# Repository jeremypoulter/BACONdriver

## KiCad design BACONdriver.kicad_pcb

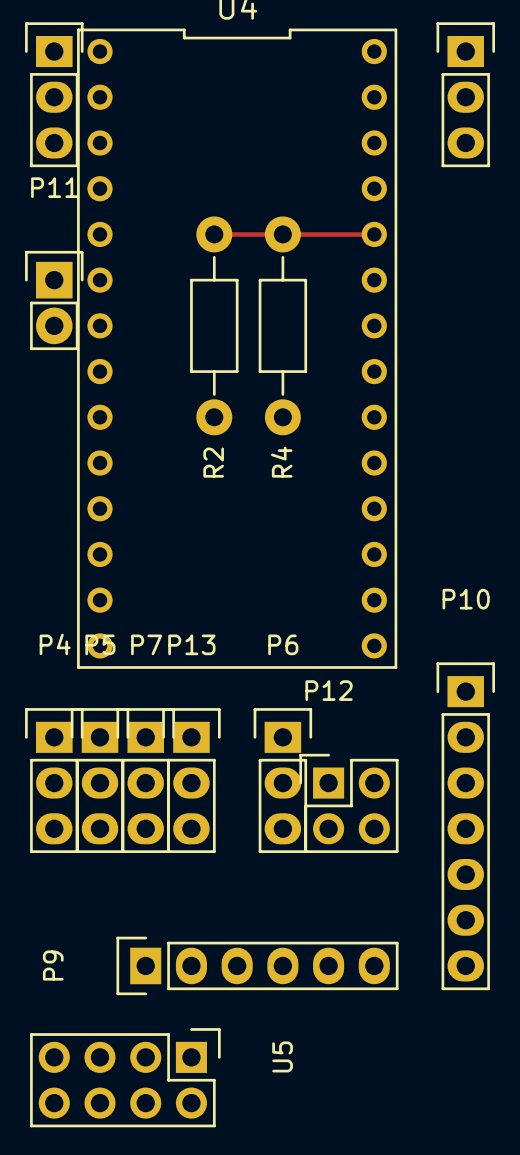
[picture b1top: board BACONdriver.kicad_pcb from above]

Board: 2 copper layers, 15 parts (0 on the bottom side), 27 nets.

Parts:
P1: Batt_Mon; Pin_Header_Straight_1x03
P4: Stearing; Pin_Header_Straight_1x03
P5: D8; Pin_Header_Straight_1x03
P6: V_Sel; Pin_Header_Straight_1x03
P7: A4; Pin_Header_Straight_1x03
P8: Batt_Current; Pin_Header_Straight_1x03
P9: FTDI; Pin_Header_Straight_1x06
P10: Motor_Ctrl; Pin_Header_Straight_1x07
P11: Batt; Pin_Header_Straight_1x02
P12: Cross; Pin_Header_Straight_2x02
P13: A5; Pin_Header_Straight_1x03
R2, R4: 10K; Resistor_Horizontal_RM10mm
U4: Metro_Mini; MetroMini
U5: nRF24L01+; Pin_Header_Straight_2x04

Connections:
+3V3: P6.1, U4.24, U5.2
+5V: P4.2, P5.2, P6.3, P7.2, P8.3, P10.7, P13.2, U4.22
+BATT: P11.2, U4.16
/Control_Board/A0: P1.2, U4.12
/Control_Board/A1: R2.1, R4.2, U4.10
/Control_Board/A4: P7.3, U4.4
/Control_Board/A5: P13.3, U4.2
/Control_Board/CS_VAL: P8.2, U4.8
/Control_Board/Cell2: P1.3, R2.2
/Control_Board/D8: P5.3, U4.17
/Control_Board/MISO: U4.25, U5.7
/Control_Board/MOSI: U4.23, U5.6
/Control_Board/NRF_CS: U4.21, U5.4
/Control_Board/NRF_ENABLE: U4.19, U5.3
/Control_Board/NRF_IRQ: U4.5, U5.8
/Control_Board/RXD: P12.1, U4.1
/Control_Board/SCK: U4.27, U5.5
/Control_Board/STEAR: P4.3, U4.7
/Control_Board/TXD: P12.4, U4.3
/Control_Board/VS_EN: P10.5, U4.15
/Control_Board/VS_INA: P10.2, U4.11
/Control_Board/VS_INB: P10.3, U4.9
/Control_Board/VS_PWM: P10.1, U4.13
GND: P1.1, P4.1, P5.1, P7.1, P8.1, P9.1, P10.6, P11.1, P13.1, R4.1, U4.18, U4.20, U5.1
unnamed: P6.2, P9.3
unnamed: P9.5, P12.2
unnamed: P9.4, P12.3

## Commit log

2015-10-15 Initial version of the electronics for BACON.
2016-02-04 KiCAD cache library file
2016-02-04 Initial version of the firmware for the BACONdriver
2016-02-10 Changes to match prototype, adding an nRF24L01 for receiving control commands from the original transmitter and an FTDI style header for future expansion.
2016-02-11 Various updates; - Break out spare pins - Use the motor driver CS for motor current (Current Sense not Chip Select) - Allow the FTDI Vcc to be switched between 3.3v and 5v
2016-02-11 Moved the components that need laying out to a sub-sheet so the net list can be generated for just those components, while also maintaining the high level wiring
2016-02-11 Initial layout of the control board to get positioning for making up on some prototyping board.
2016-02-16 Modified to use a simple voltage divider for battery voltage measurement, the op amp version would not fit on the prototype board and not really needed. Also added headers to allow the FTDI TX/RX to 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
2016-05-11 Tidy up and added some basic serial control
